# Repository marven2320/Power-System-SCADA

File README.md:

Power-System-SCADA
==================

A design and implementation of a miniaturized Power System SCADA integrated in a web-mobile application.

###Repo Merging/Pulling Rules

1. Before doing any work. Make sure you pull the latest version of `master` branch.
2. Create your own `branch`.
3. Make your modifications in your own `branch`.
4. Make sure that your work is not too behind in the `master` branch! Otherwise, you will have problems in merging your work.
5. Before merging to 'master' make sure you pull once again the lasest version of `master`.
6. Checkout to 'master' then merge your `branch` to `master`.
7. Make sure to check if the `master` branch works before you push your code to `origin`. We'll define testing methods later for everyone to do before pushing to origin. The point is not to break the master line of code.
8. If you break `master`, make sure to FIX it before Push.
9. Push all branches to `origin`.

###Basic git routine
```
1. git clone "Repo URL" folderName 
---Perform this command when you dont have the current repository you wish to contribute.
2. git pull
---Pull the current master branch in the repository.
3. git checkout -b branchName
---checkout the master branch then switches to your newly created branch "branchName".
4. git add .
--- add some files you add in the current folder/repository
5. git commit -a -m "Your commit description here"
---commit your work in the current branch
6. git checkout master
---Switch to master branch
7. git merge branchName
---Merging your recent work to master branch
8. git push origin
---Push your work to the master branch
```

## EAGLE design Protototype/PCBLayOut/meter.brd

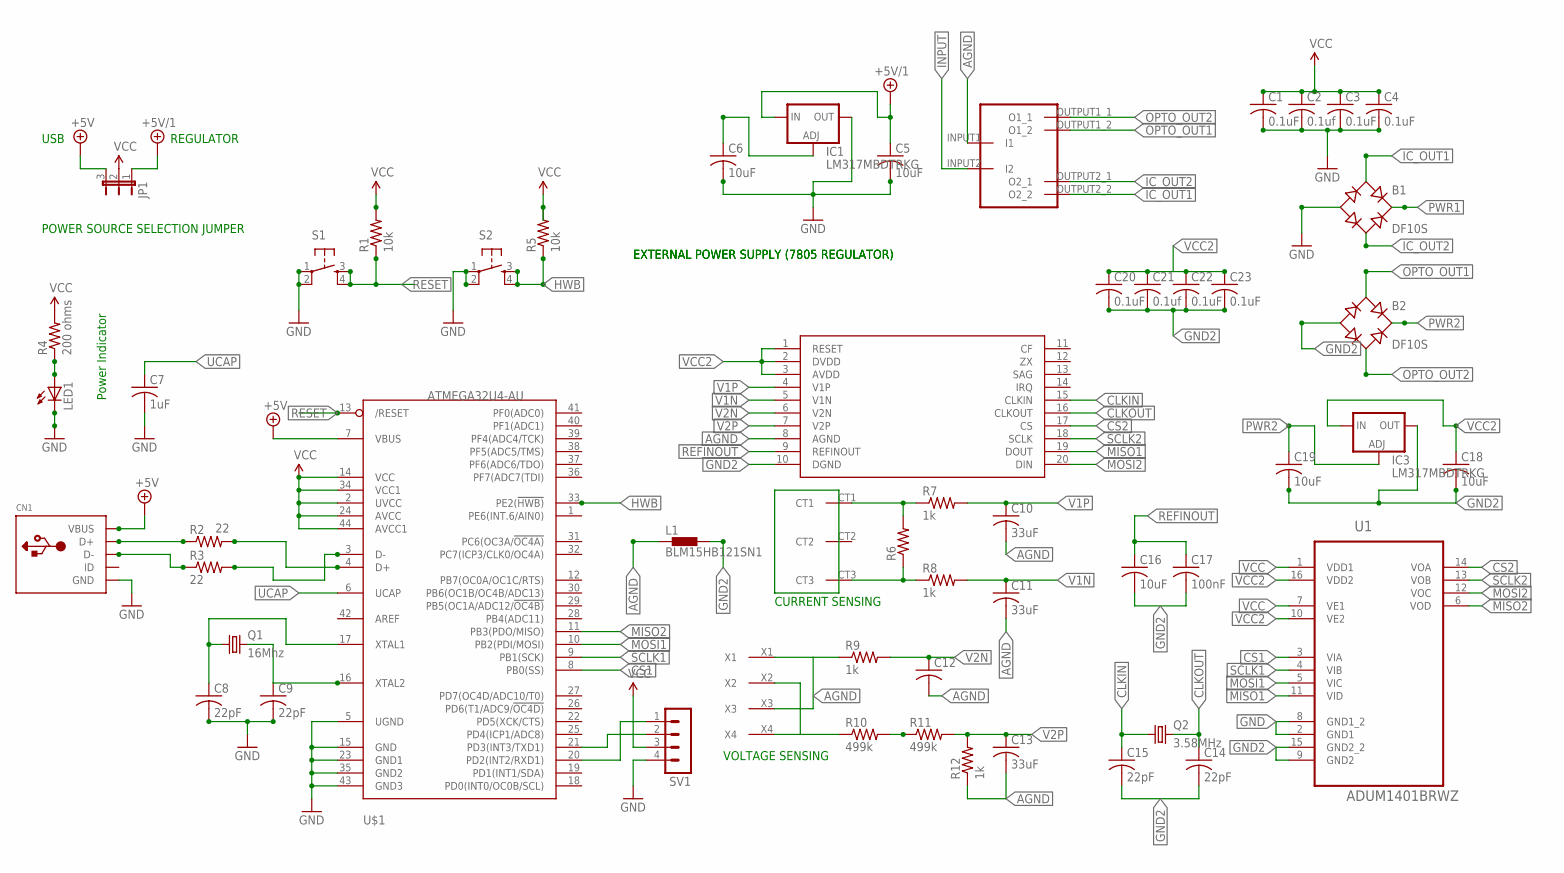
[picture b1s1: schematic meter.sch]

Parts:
B1, B2: DF10S; DFS
C1, C3, C4, C20, C22, C23: 0.1uF; C0603
C2, C21: 0.1uf; C0603
C5, C6, C16, C18, C19: 10uF; C0603
C7: 1uF; C0603
C8, C9, C14, C15: 22pF; C0603
C10, C11, C13: 33uF; C0603
C12: C-USC0603; C0603
C17: 100nF; C0603
CN1: USBMINIB; USB-MINIB
IC1, IC3: LM317MBDTRKG; DPACK
JP1: JP2E; JP2
L1: BLM15HB121SN1; 0402
LED1: LEDCHIP-LED0805; CHIP-LED0805
Q1: 16Mhz; CSM-7X-DU
Q2: 3.58MHz; CSM-7X-DU
R1, R5: 10k; 0603-RES
R2, R3: 22; 0603-RES
R4: 200 ohms; 0603-RES
R6: R-US_R0603; R0603
R7, R8, R9, R12: 1k; R0603
R10, R11: 499k; R0603
S1, S2: TAC_SWITCHSMD; TACTILE_SWITCH_SMD
SV1: MA04-1
U1: ADUM1401BRWZ; SOIC127P1032X265-16N
U$1: ATMEGA32U4-AU; TQFP44
U$2: ADE7753; SSOP20
U$3: CT; CT1075
U$4: PCB-TRANS
U$6: SCREWTERMINAL4_9.53

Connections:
+5V: CN1.VBUS, JP1.3, U$1.7 (VBUS)
+5V/1: C5.1, IC1.3 (IN), JP1.1
AGND: C10.2, C11.2, C12.2, C13.2, L1.1, R9.1, R12.1, U$2.8 (AGND), U$4.INPUT1 (I1), U$6.X1, U$6.X3
CLKIN: C15.1, Q2.1, U$2.15 (CLKIN)
CLKOUT: C14.1, Q2.2, U$2.16 (CLKOUT)
CS1: U1.3 (VIA), U$1.8 (PB0(SS))
CS2: U1.14 (VOA), U$2.17 (CS)
GND: B1.-, C1.2, C2.2, C3.2, C4.2, C5.2, C6.2, C7.2, C8.2, C9.2, CN1.GND, IC1.4 (OUT), LED1.C, S1.1, S1.2, S2.1, S2.2, SV1.4, U1.2 (GND1), U1.8 (GND1_2), U$1.5 (UGND), U$1.15 (GND), U$1.23 (GND1), U$1.35 (GND2), U$1.43 (GND3)
GND2: B2.-, C14.2, C15.2, C16.2, C17.2, C18.2, C19.2, C20.2, C21.2, C22.2, C23.2, IC3.4 (OUT), L1.2, U1.9 (GND2), U1.15 (GND2_2), U$2.10 (DGND)
HWB: R5.1, S2.3, S2.4, U$1.33 (PE2(!HWB))
IC_OUT1: B1.AC1, U$4.OUTPUT2_2 (O2_2)
IC_OUT2: B1.AC2, U$4.OUTPUT2_1 (O2_1)
INPUT: R10.1, U$4.INPUT2 (I2), U$6.X2, U$6.X4
MISO1: U1.11 (VID), U$2.19 (DOUT)
MISO2: U1.6 (VOD), U$1.11 (PB3(PDO/MISO))
MOSI1: U1.5 (VIC), U$1.10 (PB2(PDI/MOSI))
MOSI2: U1.12 (VOC), U$2.20 (DIN)
unnamed: C8.1, Q1.1, U$1.17 (XTAL1)
unnamed: R10.2, R11.1
unnamed: CN1.D+, R2.1
unnamed: R2.2, U$1.4 (D+)
unnamed: CN1.D-, R3.1
unnamed: R3.2, U$1.3 (D-)
unnamed: LED1.A, R4.1
unnamed: SV1.1, U$1.20 (PD2(INT2/RXD1))
unnamed: SV1.2, U$1.21 (PD3(INT3/TXD1))
unnamed: R6.2, R7.1, U$3.CT1
unnamed: R6.1, R8.1, U$3.CT3
unnamed: C9.1, Q1.2, U$1.16 (XTAL2)
OPTO_OUT1: B2.AC1, U$4.OUTPUT1_2 (O1_2)
OPTO_OUT2: B2.AC2, U$4.OUTPUT1_1 (O1_1)
PWR1: B1.+, C6.1, IC1.1 (ADJ)
PWR2: B2.+, C19.1, IC3.1 (ADJ)
REFINOUT: C16.1, C17.1, U$2.9 (REFINOUT)
RESET: R1.1, S1.3, S1.4, U$1.13 (/RESET)
SCLK1: U1.4 (VIB), U$1.9 (PB1(SCK))
SCLK2: U1.13 (VOB), U$2.18 (SCLK)
UCAP: C7.1, U$1.6 (UCAP)
V1N: C11.1, R8.2, U$2.5 (V1N)
V1P: C10.1, R7.2, U$2.4 (V1P)
V2N: C12.1, R9.2, U$2.6 (V2N)
V2P: C13.1, R11.2, R12.2, U$2.7 (V2P)
VCC: C1.1, C2.1, C3.1, C4.1, JP1.2, R1.2, R4.2, R5.2, SV1.3, U1.1 (VDD1), U1.7 (VE1), U$1.2 (UVCC), U$1.14 (VCC), U$1.24 (AVCC), U$1.34 (VCC1), U$1.44 (AVCC1)
VCC2: C18.1, C20.1, C21.1, C22.1, C23.1, IC3.3 (IN), U1.10 (VE2), U1.16 (VDD2), U$2.1 (RESET), U$2.2 (DVDD), U$2.3 (AVDD)

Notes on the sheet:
Power Indicator
EXTERNAL POWER SUPPLY (7805 REGULATOR)
POWER SOURCE SELECTION JUMPER
USB
REGULATOR
CURRENT SENSING
VOLTAGE SENSING

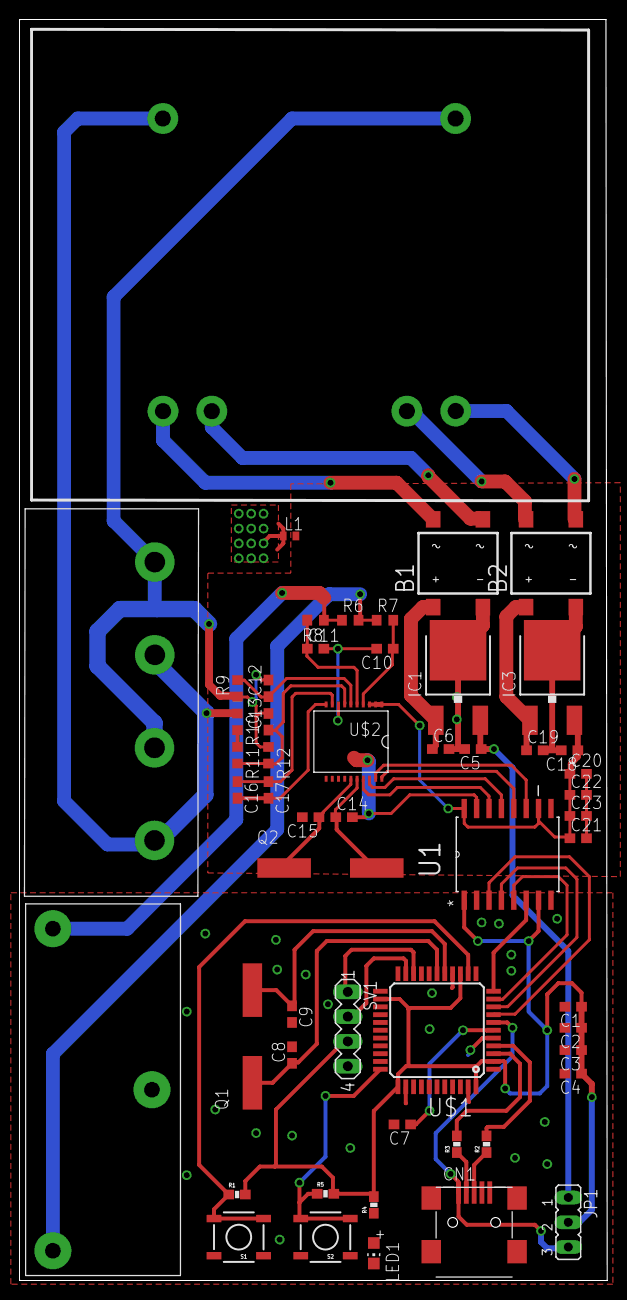
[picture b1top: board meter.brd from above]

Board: 2 copper layers, 60.2 x 129.3 mm, 54 parts (0 on the bottom side), 44 nets.

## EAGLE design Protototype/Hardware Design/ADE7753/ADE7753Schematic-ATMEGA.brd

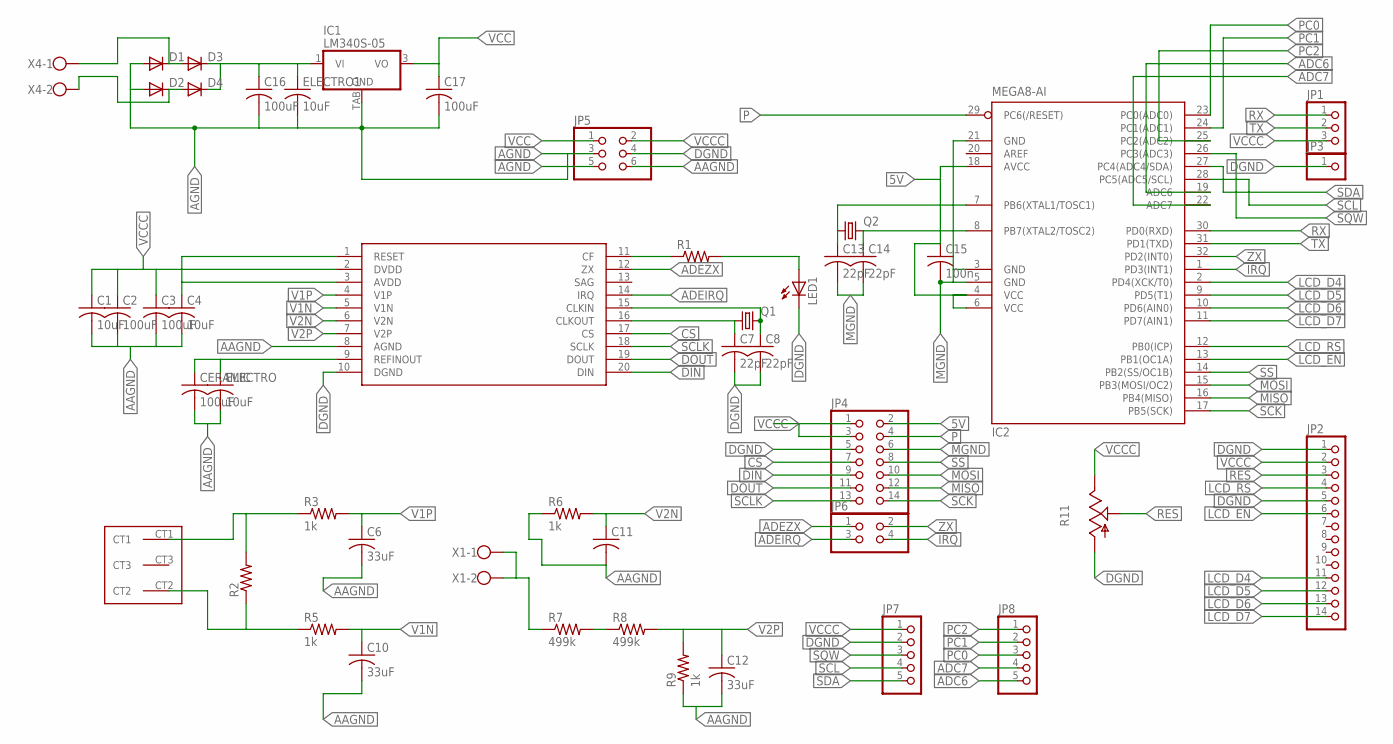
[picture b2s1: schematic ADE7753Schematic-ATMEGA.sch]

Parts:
C1, C4: 10uF; C025-030X050
C2, C3, C16, C17: 100uF; C0603K
C6, C10, C12: 33uF; C0805K
C7, C8, C13, C14: 22pF; C0603K
C11: C-USC0805K; C0805K
C15: 100n; C0603K
CERAMIC: 100uF; C0603K
D1, D2, D3, D4: DIODE-SMB; SMB
ELECTRO, ELECTRO1: 10uF; C025-030X050
IC1: LM340S-05; TO263-3
IC2: MEGA8-AI; TQFP32-08
JP1: PINHD-1X3CB; 1X03-CLEANBIG
JP2: PINHD-1X14-CB; 1X14-CB
JP3: PINHD-1X1CB; 1X01-CLEANBIG
JP4: PINHD-2X7; 2X07
JP5: PINHD-2X3; 2X03
JP6: PINHD-2X2; 2X02
JP7, JP8: PINHD-1X5; 1X05
LED1: LEDCHIPLED_0805; CHIPLED_0805
Q1: CRYSTALHC49S; HC49/S
Q2: CRYSTALHC49UP; HC49UP
R1: R-US_R1206; R1206
R2: R-US_0309/12; 0309/12
R3, R5, R6, R9: 1k; R1206
R7, R8: 499k; R1206
R11: TRIM_US-RJ9W; RJ9W
U$1: ADE7753; SSOP20
U$2: CURRENTXFORMER; 3PINS
X1: W239-302
X4: W237-102

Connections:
5V: C15.1, IC2.4 (VCC), IC2.6 (VCC), IC2.18 (AVCC), JP4.2
AAGND: C1.2, C2.2, C3.2, C4.2, C6.2, C10.2, C11.2, C12.2, CERAMIC.2, ELECTRO.2, JP5.6, R6.1, R9.1, U$1.8 (AGND)
ADC6: IC2.19 (ADC6), JP8.5
ADC7: IC2.22 (ADC7), JP8.4
ADEIRQ: JP6.3, U$1.14 (IRQ)
ADEZX: JP6.1, U$1.12 (ZX)
AGND: C16.2, C17.2, D1.A, D2.A, ELECTRO1.2, IC1.TAB (GND), JP5.3, JP5.5
CS: JP4.7, U$1.17 (CS)
DGND: C7.2, C8.2, JP2.1, JP2.5, JP3.1, JP4.5, JP5.4, JP7.2, LED1.C, R11.A, U$1.10 (DGND)
DIN: JP4.9, U$1.20 (DIN)
DOUT: JP4.11, U$1.19 (DOUT)
IRQ: IC2.1 (PD3(INT1)), JP6.4
LCD_D4: IC2.2 (PD4(XCK/T0)), JP2.11
LCD_D5: IC2.9 (PD5(T1)), JP2.12
LCD_D6: IC2.10 (PD6(AIN0)), JP2.13
LCD_D7: IC2.11 (PD7(AIN1)), JP2.14
LCD_EN: IC2.13 (PB1(OC1A)), JP2.6
LCD_RS: IC2.12 (PB0(ICP)), JP2.4
MGND: C13.2, C14.2, C15.2, IC2.3 (GND), IC2.5 (GND), IC2.21 (GND), JP4.6
MISO: IC2.16 (PB4(MISO)), JP4.12
MOSI: IC2.15 (PB3(MOSI/OC2)), JP4.10
unnamed: D1.C, D3.A, X4.1
unnamed: C8.1, Q1.2, U$1.15 (CLKIN)
unnamed: CERAMIC.1, ELECTRO.1, U$1.9 (REFINOUT)
unnamed: C7.1, Q1.1, U$1.16 (CLKOUT)
unnamed: R1.1, U$1.11 (CF)
unnamed: LED1.A, R1.2
unnamed: R2.2, R3.1, U$2.CT1
unnamed: R2.1, R5.1, U$2.CT2
unnamed: R7.2, R8.1
unnamed: C14.1, IC2.8 (PB7(XTAL2/TOSC2)), Q2.2
unnamed: R7.1, X1.1, X1.2
unnamed: C13.1, IC2.7 (PB6(XTAL1/TOSC1)), Q2.1
unnamed: D2.C, D4.A, X4.2
unnamed: C16.1, D3.C, D4.C, ELECTRO1.1, IC1.1 (VI)
P: IC2.29 (PC6(/RESET)), JP4.4
PC0: IC2.23 (PC0(ADC0)), JP8.3
PC1: IC2.24 (PC1(ADC1)), JP8.2
PC2: IC2.25 (PC2(ADC2)), JP8.1
RES: JP2.3, R11.S
RX: IC2.30 (PD0(RXD)), JP1.1
SCK: IC2.17 (PB5(SCK)), JP4.14
SCL: IC2.28 (PC5(ADC5/SCL)), JP7.4
SCLK: JP4.13, U$1.18 (SCLK)
SDA: IC2.27 (PC4(ADC4/SDA)), JP7.5
SQW: IC2.26 (PC3(ADC3)), JP7.3
SS: IC2.14 (PB2(SS/OC1B)), JP4.8
TX: IC2.31 (PD1(TXD)), JP1.2
V1N: C10.1, R5.2, U$1.5 (V1N)
V1P: C6.1, R3.2, U$1.4 (V1P)
V2N: C11.1, R6.2, U$1.6 (V2N)
V2P: C12.1, R8.2, R9.2, U$1.7 (V2P)
VCC: C17.1, IC1.3 (VO), JP5.1
VCCC: C1.1, C2.1, C3.1, C4.1, JP1.3, JP2.2, JP4.1, JP4.3, JP5.2, JP7.1, R11.E, U$1.1 (RESET), U$1.2 (DVDD), U$1.3 (AVDD)
ZX: IC2.32 (PD2(INT0)), JP6.2

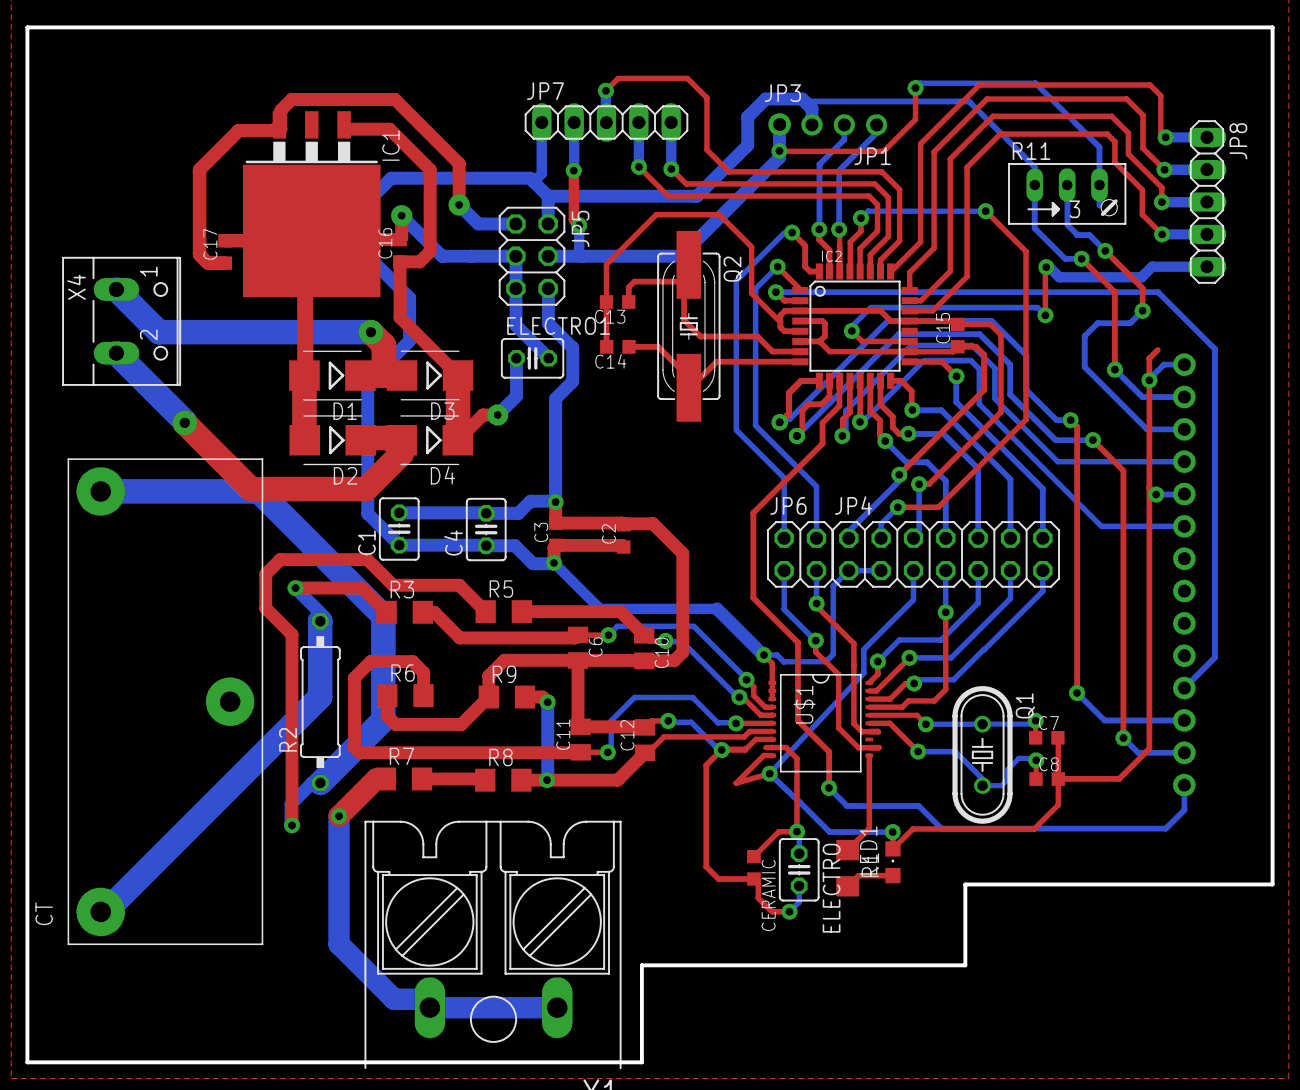
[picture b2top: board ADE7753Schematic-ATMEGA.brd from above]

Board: 2 copper layers, 97.8 x 81.3 mm, 48 parts (0 on the bottom side), 55 nets.

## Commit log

2014-11-19 Updated Repo Rules
2014-11-19 Creating Subfolders
2014-11-19 Adding readme file to all folders
2014-11-19 added test.md to server folder
2014-11-19 added additional texts on test.md
2014-11-22 Testing Edit
2014-11-26 proposal one-line diagram
2014-11-28 Adding some folders
2014-11-28 deleting some files
2014-11-29 Practice coding js and html
2014-12-03 Added files on Hardware Design for the circuit diagram of the board
2014-12-06 Tentative pcb meter design
2014-12-07 Updating my Client Folder
2014-12-07 Updating my CSS files for layouting.
2014-12-07 Updating my Homepage Client
2015-01-14 Added folders: PCBLayout which contains the updated pcb design and TempCost which contains the temporary cart for purchasing the components with cost and papers
2015-08-11 adding the index file
2015-08-11 Adding my Final Client Project Folder Name: iMonitor

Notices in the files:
parts and their libraries:
SparkFun-Passives: Licensing: CC v3.0 Share-Alike You are welcome to use this library for commercial purposes.
